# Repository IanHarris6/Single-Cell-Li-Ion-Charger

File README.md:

# MCP7382T-2DCI Breakout Board

The schematic above is a simple breakout board designed to evaluate the MCP73832 IC. This IC is capable of charging a single Li-Ion cell to its fully voltage of 4.2 Volts and will stop supplying current to the battery once it has been fully charged.

Components:

C1,C2-Filtering Capacitors

D1-ESD Protection

D2-Status LED indicator

J1-Micro USB type B input for power

J2,J3,J4,J5,J6-Access to each pin of the MCP73832

Rled-Current limiting resistor for the status LED

Rprog-Program resistor which determines the charge current. See figure 2-4 in datasheet to determine charge current.

U1-MCP73832-2DCI, single cell Li-Ion charger IC.

Pin Description:

1-STAT-OUTPUT. Low indicates charging, HIGH Z indicates charge cycle complete, no battery present, or shutdown.

2-VSS-GND. Pin header connects to negative termnial of Li-Ion cell.

3-VBAT-POWER OUTPUT. Pin header connects to positive termnial of Li-Ion cell.

4-VDD-POWER INPUT. Use Vbus from Micro USB to power MCP7382T

5-PROG-DIGITAL INPUT. Current regulation input pin. Left floating or applying a logic-high input signal disables device and terminates charge cycle.

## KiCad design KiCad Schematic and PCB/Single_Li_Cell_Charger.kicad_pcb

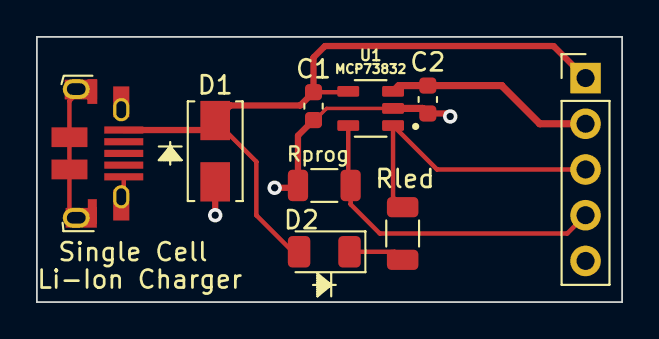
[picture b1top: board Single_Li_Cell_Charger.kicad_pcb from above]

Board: 2 copper layers, 32.5 x 14.7 mm, 9 parts (0 on the bottom side), 6 nets.

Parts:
C1, C2: 4.7uF; C_0603_1608Metric
D1: SMAJ5.0; SMAJ5.0A
D2: LED; D_1206_3216Metric
J1: USB_B_Micro; micro_usb_b_2.0_horizontal
J4: Conn_01x05; PinHeader_1x05_P2.54mm_Vertical
Rled: 470; R_1206_3216Metric
Rprog: 2k; R_1206_3216Metric
U1: MCP73832T-2DCI/OT; SOT95P280X145-5N

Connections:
+BATT: C2.1, J4.2, U1.3 (VBAT)
-BATT: C1.2, C2.2, D1.2 (A), J1.5 (GND), J1.6 (Shield), J4.5, Rprog.2, U1.2 (VSS)
/PROG: J4.4, Rprog.1, U1.5 (PROG)
/STAT: J4.3, Rled.2, U1.1 (STAT)
unnamed: D2.1 (K), Rled.1
VBUS: C1.1, D1.1 (K), D2.2 (A), J1.1 (VBUS), J4.1, U1.4 (VDD)

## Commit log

2022-12-31 Version 1.0
2023-01-06 V2
    V2- Updated MicroUSB footprint and changed header pins so it will fit a row of pin headers instead of them being spaced out.
2023-01-06 Updating read me with V2 schematic
    V2 PCB corrected micro usb footprint and pin headers
2023-01-07 Edge Cuts Fixed
2023-01-07 New PCB file

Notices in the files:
parts and their libraries:
Copyright 2021 Accelerated Designs. All rights reserved.
